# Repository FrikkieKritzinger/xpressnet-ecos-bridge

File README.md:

# OmniConnect (XpressNet-Ecos Bridge)

A protocol bridge on a Wemos D1 Mini (ESP8266) that lets XpressNet throttles (Roco MultiMaus), Z21 LAN throttles (Roco WLANmaus / Z21 apps), LocoNet throttles (Digitrax UT6) and an ESU Ecos command station control the same locomotives and accessories, with every change propagated to all of them.

**Status:** Working on real hardware (Phases 1-6 complete, Phase 7 in progress; LocoNet released).
**Target Platform:** ESP8266 (Wemos D1 Mini)
**Firmware version:** see `xpressnet_ecos_bridge/version.h` (currently 1.5.4)

See [CLAUDE.md](CLAUDE.md) for current architecture and status, and [docs/CHANGELOG.md](docs/CHANGELOG.md) for the dated development history.

## What it does

- **XpressNet** (hardwired RS485, timing-critical) - acts as the bus *master* for MultiMaus-style throttles, built on Philipp Gahtow's XpressNetMaster library. Speed, direction, F0-F28, track power / emergency stop and turnouts.
- **Ecos LAN** (WiFi, TCP port 15471) - ESU's plain-text object protocol (not XML). Speed, direction, functions, emergency stop and accessories, in both directions.
- **Z21 LAN** (WiFi, UDP port 21105) - emulates a Z21 so a WLANmaus or Z21 app can connect straight to the bridge.
- **LocoNet** (hardware on the motherboard PCB, receive on UART0, transmit via SoftwareSerial) - acts as a slot server for Digitrax throttles such as the UT6: speed, direction, F0-F28, track power / stop and turnouts. Slot ownership is internal and never blocks other protocols.
- **State engine** - in-memory tracking of up to 50 active locomotives; a loco is dropped (and unsubscribed from Ecos) after 5 minutes of inactivity.
- **OLED display** (128x64 SSD1306) - six status pages (main, device, XpressNet, Ecos, Z21, LocoNet) plus a boot splash.
- **Setup Mode** - a Wi-Fi access point and web page to edit the persisted settings and to upload new firmware over the air.

Design premise: any command from any throttle protocol is forwarded to Ecos *and* to every other throttle-facing protocol; Ecos is the only required, known device. There is no exclusive ownership of a locomotive between protocols.

## Hardware

- **MCU:** Wemos D1 Mini (ESP8266, 80/160 MHz single core, 4 MB flash, 160 KB RAM). ESP32 is a possible future "v3", not a supported target (see CLAUDE.md, "MCU Platform").
- **XpressNet:** MAX485 RS485 module, wired the way Gahtow's Z21 command station does it - a *single* half-duplex data pin (DI and RO tied together) and a *single* direction pin (DE and RE tied together).
- **Display:** SSD1306 128x64 I2C OLED.
- **Setup button:** momentary pushbutton to GND.

### Pin map (as implemented in `config.h`)

| Function | D1 Mini pin | GPIO | Notes |
|----------|-------------|------|-------|
| XpressNet data (SoftwareSerial RX+TX) | D6 | 12 | 62500 baud, 8 data bits + parity used as the 9th (call-byte) bit |
| XpressNet MAX485 DE+RE | D0 | 16 | HIGH = transmit, LOW = receive |
| OLED SDA | D2 | 4 | I2C, address 0x3C |
| OLED SCL | D1 | 5 | I2C |
| Setup Mode button | D7 | 13 | to GND, internal pull-up; hold 3 s |
| LocoNet TX / RX | D3 / RX | 0 / 3 | TX through a BC547 (inverted), RX on hardware UART0 16660 baud, per Gahtow's D1 Mini design |

The LocoNet pins share boot-strap and USB-serial lines: UART0 belongs to LocoNet, so USB flashing and serial debug are unavailable while the D1 is seated. Flash with the D1 removed, or over the network with the `wemos_dev` environment and `tools/devflash.py`; read debug text from the TCP log on port 23 (`tools/netlog.py`).

## Getting started

### Prerequisites

- [PlatformIO](https://platformio.org/) (`pip install platformio`)
- Libraries are resolved by PlatformIO (`Adafruit SSD1306`); Gahtow's XpressNetMaster is vendored in `libraries/XpressNetMaster/` (with local modifications - see CLAUDE.md).

### Build and flash

1. Copy `xpressnet_ecos_bridge/wifi_credentials.local.h.example` to `xpressnet_ecos_bridge/wifi_credentials.local.h` and fill in your Wi-Fi SSID and password. This file is gitignored; never commit it.
2. Review `xpressnet_ecos_bridge/config.h` (the Ecos IP default and feature toggles live there).
3. Build and flash:
   ```bash
   python -m platformio run -e wemos
   python -m platformio run -e wemos -t upload
   ```
4. Serial monitor at 115200 baud (`monitor_rts`/`monitor_dtr` are disabled so opening the monitor does not reset the board).

### First boot and configuration

The settings that vary per installation live in EEPROM, not in the firmware: Wi-Fi SSID/password, Ecos IP, the bridge's own **static** IP / gateway / subnet (mandatory - there is no DHCP), the XpressNet bus timeout and the loco inactivity timeout. `config.h` only supplies defaults used to seed the EEPROM.

On first boot (or whenever the config is incomplete) the bridge starts **Setup Mode**: join the open `OmniConnect-Setup` Wi-Fi network and browse to the page it shows on the OLED. You can also enter Setup Mode by holding the pushbutton for 3 seconds, or automatically after 5 minutes of continuous Wi-Fi loss. The same Setup Mode serves `/update`, a firmware upload page (OTA).

### Tests

Unit tests run natively on the host (no hardware). From the repository root, with a MinGW/GCC toolchain on PATH:

```bash
python -m platformio test -e native
```

408 tests currently pass. See [test/README.md](test/README.md).

## Repository structure

```
.
├── README.md, CLAUDE.md, platformio.ini
├── docs/                       Design docs, protocol specs, CHANGELOG.md
├── libraries/XpressNetMaster/  Vendored Gahtow XpressNet master library
├── test/                       Native unit tests (Unity) + mocks/fixtures
└── xpressnet_ecos_bridge/      Firmware sources (PlatformIO src_dir)
    ├── xpressnet_ecos_bridge.ino   setup()/loop()
    ├── config.h, version.h, definitions.h
    ├── state_engine.*, command_router.*
    ├── eeprom_config.*, eeprom_store.*     Persisted settings
    ├── setup_mode.*, setup_web_form.*      Setup Mode AP/web UI/OTA
    ├── oled_display.cpp, display/
    ├── interfaces/interface_base.h         ProtocolInterface contract
    ├── protocols/{xpressnet,ecos,z21lan,loconet}/
    └── utils/
```

A file-by-file list is in [docs/03_FILE_MANIFEST.md](docs/03_FILE_MANIFEST.md).

## Documentation

- [CLAUDE.md](CLAUDE.md) - current architecture, conventions, configuration and status
- [docs/CHANGELOG.md](docs/CHANGELOG.md) - dated history and diagnoses
- [docs/user/](docs/user/) - user documentation sources (Quick Start Guide, User Manual); build the Word files with `python tools/build_docs.py`
- [docs/01_DESIGN_DOCUMENT.md](docs/01_DESIGN_DOCUMENT.md) - architecture and design
- [docs/02_PHASE_3_2_ECOS_DESIGN.md](docs/02_PHASE_3_2_ECOS_DESIGN.md) - Ecos interface design
- [docs/03_FILE_MANIFEST.md](docs/03_FILE_MANIFEST.md) - source file inventory
- [docs/04_PHASE_4_TESTING_INFRASTRUCTURE.md](docs/04_PHASE_4_TESTING_INFRASTRUCTURE.md) - test infrastructure plan and outcome

## Attribution

Inspired by and built on the work of Philipp Gahtow:
- [Z21 Command Station](https://pgahtow.de/w/Zentrale_Z21PG/en) - architecture patterns and wiring
- [XpressNet](https://pgahtow.de/w/XpressNet) and the XpressNetMaster library
- [LocoNet](https://pgahtow.de/w/Loconet) write-up and hardware designs

## License

See [LICENSE](LICENSE).

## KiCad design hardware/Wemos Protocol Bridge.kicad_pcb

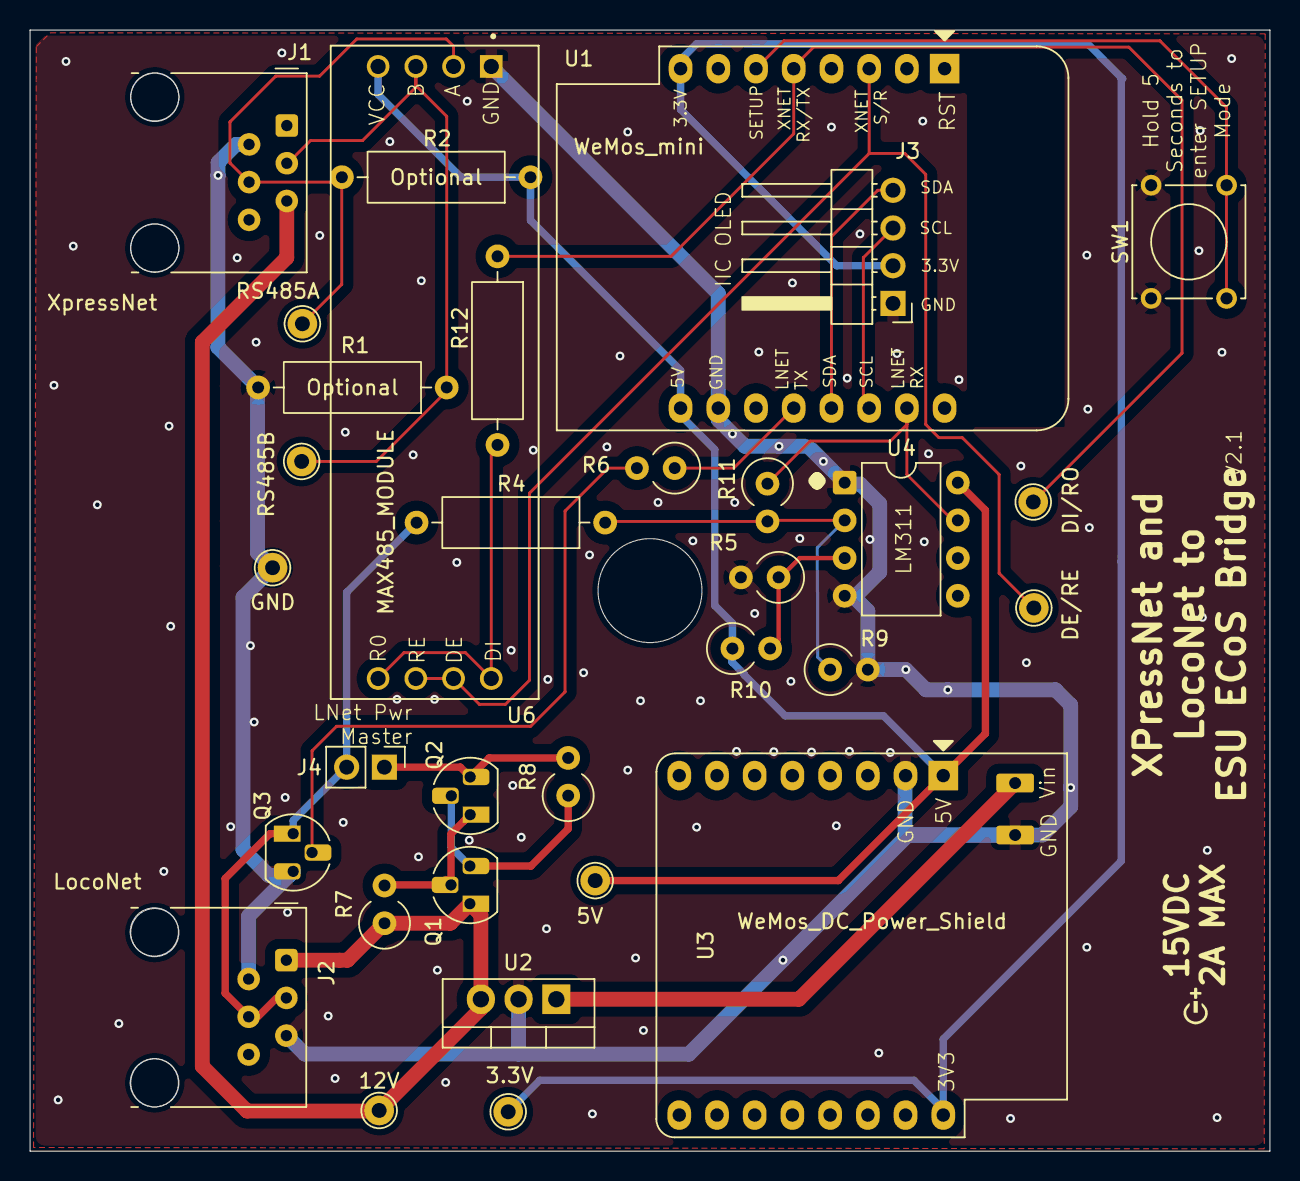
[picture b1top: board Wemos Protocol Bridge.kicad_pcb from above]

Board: 2 copper layers, 83.5 x 75.5 mm, 32 parts (0 on the bottom side), 22 nets.

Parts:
3.3V: TP 3.3V; TestPoint_Pad_D2.0mm
5V: TP 5V; TestPoint_Pad_D2.0mm
12V: TP 12V; TestPoint_Pad_D2.0mm
DE/RE: TP DE/RE; TestPoint_Pad_D2.0mm
DI/RO: TP DI/RO; TestPoint_Pad_D2.0mm
GND: TP GND; TestPoint_Pad_D2.0mm
J1: XpressNet; RJ12_Amphenol_54601-x06_Horizontal
J2: LocoNet; RJ12_Amphenol_54601-x06_Horizontal
J3: Conn_01x04_Pin; PinHeader_1x04_P2.54mm_Horizontal
J4: Conn_01x02; PinHeader_1x02_P2.54mm_Vertical
Q1, Q2, Q3: BC547; TO-92L_HandSolder
R1, R2: 2.2k; R_Axial_DIN0309_L9.0mm_D3.2mm_P12.70mm_Horizontal
R4: 47k; R_Axial_DIN0309_L9.0mm_D3.2mm_P12.70mm_Horizontal
R5: 22k; R_Axial_DIN0309_L9.0mm_D3.2mm_P2.54mm_Vertical
R6: 4.7k; R_Axial_DIN0309_L9.0mm_D3.2mm_P2.54mm_Vertical
R7, R10: 10k; R_Axial_DIN0309_L9.0mm_D3.2mm_P2.54mm_Vertical
R8: 47R; R_Axial_DIN0309_L9.0mm_D3.2mm_P2.54mm_Vertical
R9: 150k; R_Axial_DIN0309_L9.0mm_D3.2mm_P2.54mm_Vertical
R11: 220k; R_Axial_DIN0309_L9.0mm_D3.2mm_P2.54mm_Vertical
R12: 330R; R_Axial_DIN0309_L9.0mm_D3.2mm_P12.70mm_Horizontal
RS485A: TP RS458 A; TestPoint_Pad_D2.0mm
RS485B: TP RS458 B; TestPoint_Pad_D2.0mm
SW1: SW_SPST; SW_Tactile_Straight_KSA0Axx1LFTR
U1: WeMos_mini; WEMOS_D1_mini_light
U2: LM7812_TO220; TO-220-3_Vertical
U3: WeMos_DC_Power_Shield; WEMOS_DC_POWER_SHIELD
U4: LM311; DIP-8_W7.62mm
U6: MAX485_MODULE; MODULE_MAX485_MODULE_5V_LOGIC_TLL_TO_RS-485_CONVERTER

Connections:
+3.3V: 3.3V.1 (1_1), J3.2, U1.8 (3.3V), U3.16 (3.3V)
+5V: 5V.1 (1_1), R2.1, R10.1, U1.9 (5V), U3.1 (5V), U4.8 (V+), U6.4 (VCC)
+12V: 12V.1 (1_1), J1.5, J2.1, Q1.1 (C), R7.1, U2.3 (VO)
GND: GND.1 (1_1), J1.2, J2.2, J2.5, J3.1, Q3.3 (E), R1.2, R5.2, R9.2, SW1.1 (A), U1.10 (GND), U2.2 (GND), U3.2 (GND), U3.17 (GND), U4.1 (GND), U4.4 (V-), U6.1 (GND)
unnamed: J3.3, U1.14 (D1)
unnamed: J3.4, U1.13 (D2)
unnamed: J4.1, Q2.3 (E), R8.2
unnamed: J2.3, J2.4, J4.2, Q3.1 (C), R4.2
unnamed: Q1.2 (B), Q2.1 (C), R7.2
unnamed: Q1.3 (E), Q2.2 (B), R8.1
unnamed: Q3.2 (B), R6.2
unnamed: SW1.2 (B), U1.6 (D7)
unnamed: DE/RE.1 (1_1), U1.3 (D0), U6.6 (RE), U6.7 (DE)
unnamed: R6.1, U1.12 (D3)
unnamed: DI/RO.1 (1_1), R12.1, U1.5 (D6)
unnamed: R11.1, U1.15 (Rx), U4.7
unnamed: U2.1 (VI), U3.18 (VCC)
unnamed: R4.1, R9.1, R11.2, U4.2 (+)
unnamed: R5.1, R10.2, U4.3 (-)
unnamed: J1.4, R2.2, RS485A.1 (1_1), U6.2 (A)
unnamed: J1.3, R1.1, RS485B.1 (1_1), U6.3 (B)
unnamed: R12.2, U6.5 (RO), U6.8 (DI)

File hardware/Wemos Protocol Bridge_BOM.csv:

"Reference","Qty","Value","DNP","Exclude from BOM","Exclude from Board","Footprint","Datasheet"
"3.3V_TP3","1","TP 3.3V","","","","TestPoint:TestPoint_Pad_D2.0mm",""
"5V_TP1","1","TP 5V","","","","TestPoint:TestPoint_Pad_D2.0mm",""
"12V_TP2","1","TP 12V","","","","TestPoint:TestPoint_Pad_D2.0mm",""
"D1","1","1N4004 - removed due to power issues on D1","","","Excluded from board","Diode_THT:D_DO-41_SOD81_P10.16mm_Horizontal","http://www.vishay.com/docs/88503/1n4001.pdf"
"DE/RE_TP6","1","TP DE/RE","","","","TestPoint:TestPoint_Pad_D2.0mm",""
"DI/RO_TP5","1","TP DI/RO","","","","TestPoint:TestPoint_Pad_D2.0mm",""
"GND_TP4","1","TP GND","","","","TestPoint:TestPoint_Pad_D2.0mm",""
"J1","1","XpressNet","","","","Connector_RJ:RJ12_Amphenol_54601-x06_Horizontal",""
"J2","1","LocoNet","","","","Connector_RJ:RJ12_Amphenol_54601-x06_Horizontal",""
"J3","1","Conn_01x04_Pin","","","","Connector_PinHeader_2.54mm:PinHeader_1x04_P2.54mm_Horizontal",""
"J4","1","Conn_01x02","","","","Connector_PinHeader_2.54mm:PinHeader_1x02_P2.54mm_Vertical",""
"Q1,Q2,Q3","3","BC547","","","","Package_TO_SOT_THT:TO-92L_HandSolder","https://www.onsemi.com/pub/Collateral/BC550-D.pdf"
"R1,R2","2","2.2k","","","","Resistor_THT:R_Axial_DIN0309_L9.0mm_D3.2mm_P12.70mm_Horizontal",""
"R4","1","47k","","","","Resistor_THT:R_Axial_DIN0309_L9.0mm_D3.2mm_P12.70mm_Horizontal",""
"R5","1","22k","","","","Resistor_THT:R_Axial_DIN0309_L9.0mm_D3.2mm_P2.54mm_Vertical",""
"R6","1","4.7k","","","","Resistor_THT:R_Axial_DIN0309_L9.0mm_D3.2mm_P2.54mm_Vertical",""
"R7,R10","2","10k","","","","Resistor_THT:R_Axial_DIN0309_L9.0mm_D3.2mm_P2.54mm_Vertical",""
"R8","1","47R","","","","Resistor_THT:R_Axial_DIN0309_L9.0mm_D3.2mm_P2.54mm_Vertical",""
"R9","1","150k","","","","Resistor_THT:R_Axial_DIN0309_L9.0mm_D3.2mm_P2.54mm_Vertical",""
"R11","1","220k","","","","Resistor_THT:R_Axial_DIN0309_L9.0mm_D3.2mm_P2.54mm_Vertical",""
"R12","1","330R","","","","Resistor_THT:R_Axial_DIN0309_L9.0mm_D3.2mm_P12.70mm_Horizontal",""
"RS485A_TP8","1","TP RS458 A","","","","TestPoint:TestPoint_Pad_D2.0mm",""
"RS485B_TP7","1","TP RS458 B","","","","TestPoint:TestPoint_Pad_D2.0mm",""
"SW1","1","SW_SPST","","","","Button_Switch_THT:SW_Tactile_Straight_KSA0Axx1LFTR",""
"U1","1","WeMos_mini","","","","RF_Module:WEMOS_D1_mini_light","http://www.wemos.cc/Products/d1_mini.html"
"U2","1","LM7812_TO220","","","","Package_TO_SOT_THT:TO-220-3_Vertical","https://www.onsemi.cn/PowerSolutions/document/MC7800-D.PDF"
"U3","1","WeMos_DC_Power_Shield","","","","library:WEMOS_DC_POWER_SHIELD","http://www.wemos.cc/Products/d1_mini.html"
"U4","1","LM311","","","","Package_DIP:DIP-8_W7.62mm","https://www.st.com/resource/en/datasheet/lm311.pdf"
"U5","1","ER_OLEDM0.91_1x-I2C","","","","Display:ER_OLEDM0.91_1x-I2C","https://www.buydisplay.com/download/manual/ER-OLEDM0.91-1_Da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"
"U6","1","MAX485_MODULE","","","","MAX485_MODULE_5V_LOGIC_TLL_TO_RS-485_CONVERTER:MODULE_MAX485_MODULE_5V_LOGIC_TLL_TO_RS-485_CONVERTER",""
